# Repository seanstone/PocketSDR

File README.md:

# **Pocket SDR - An Open-Source GNSS SDR, ver. 0.12**

## **Modifications**

* Add .gitignore
* Submodules for LDPC-codes and libfec
* Ignore untracked in libfec submodule
* Executable python scripts
* Use pkg-config for compiler args
* Top-level makefile
* macOS support

--------------------------------------------------------------------------------

## **Overview**

Pocket SDR is an open-source GNSS (Global Navigation Satellite System) receiver
based on the SDR (software defined radio) technology. It consists of RF frontend
devices named "Pocket SDR FE", some utilities for the devices, and GNSS-SDR
APs (application programs) written in Python, C, and C++. It supports almost all
signals for GPS, GLONASS, Galileo, QZSS, BeiDou, NavIC, and SBAS.

The Pocket SDR FE device consists of 2 or 4 RF frontend channels, which support
GNSS L1 band (1525 - 1610 MHz), or L2/L5/L6 band (1160 - 1290 MHz). The bandwidth
of each RF channel covers up to 36 MHz. The sampling rate of the ADC can be
configured up to 32 Msps (FE 2CH) or 48 Msps (FE 4CH).

The Pocket SDR also contains some utility programs for the Pocket SDR FE devices,
to setup the devices, capture and dump the digitized IF (inter-frequency) data.
These utilities support Windows, Linux, Raspberry Pi OS, and other environments.
The Pocket SDR also provides GNSS-SDR APs to show the PSD (power spectrum
density) of captured IF data, search GNSS signals, track these signals, decode
navigation data and generate PVT (position, velocity and time) solutions. The
supported GNSS signals are as follows. For details on these signals and signal
IDs used in the APs, refer [Pocket SDR Signal IDs](/doc/signal_IDs.pdf).

* **GPS**: L1C/A, L1C-D, L1C-P, L2C-M, L5-I, L5-Q
* **GLONASS**: L1C/A (L1OF), L2C/A (L2OF), L1OCd, L1OCp, L2OCp, L3OCd, L3OCp
* **Galileo**: E1-B, E1-C, E5a-I, E5a-Q, E5b-I, E5b-Q, E6-B, E6-C
* **QZSS**: L1C/A, L1C/B, L1C-D, L1C-P, L1S, L2C-M, L5-I, L5-Q, L5S-I, L5S-Q, L6D, L6E
* **BeiDou**: B1I, B1C-D, B1C-P, B2a-D, B2a-P, B2I, B2b-I, B3I
* **NavIC**: L1-SPS-D, L1-SPS-P, L5-SPS
* **SBAS**: L1C/A, L5-I, L5-Q

These utilities and APs are written in Python, C, and C++ by very compact way. They
are easily modified by users to add user's unique algorithms. 

**<p style="text-align: center;">Pocket SDR FEs (FE 2CH v.2.1, FE 2CH v.2.3, and FE 4CH v.3.0)</p>**

The introduction of Pocket SDR is shown in the following slides.

T.Takasu, An Open Source GNSS SDR: Development and Application, IPNTJ Next GNSS
Technology WG, Feb 21, 2022
(https://gpspp.sakura.ne.jp/paper2005/IPNTJ_NEXTWG_202202.pdf)

For an application of Pocket SDR, refer the following slides.

T.Takasu, Development of QZSS L6 Receiver without Pilot Signal by using SDR,
IPNTJ Annual Conference, June 10, 2022
(https://gpspp.sakura.ne.jp/paper2005/IPNTJ_20220610.pdf)

--------------------------------------------------------------------------------

## **Directory Structure and Contents**
```
PocketSDR --+-- bin     Pocket SDR APs binary programs
            +-- app     Pocket SDR APs source programs
            |   +-- pocket_conf  Pocket SDR FE device configurator
            |   +-- pocket_dump  Dump digital IF data of Pocket SDR FE device
            |   +-- pocket_scan  Scan and list USB devices
            |   +-- pocket_acq   GNSS signal acquisition
            |   +-- pocket_trk   GNSS signal tracking and PVT generation
            |   +-- pocket_snap  Snapshot Positioning
            +-- src     Pocket SDR library source programs
            +-- python  Pocket SDR Python scripts
            +-- lib     Libraries for APs and Python scripts
            |   +-- win32        Libraries for Windows
            |   +-- linux        Libraries for Linux or Raspberry Pi OS
            |   +-- build        Makefiles to build libraries
            |   +-- cyusb        Cypress EZ-USB API (CyAPI.a) and includes
            |   +-- RTKLIB       RTKLIB source programs based on 2.4.3 b34
            |   +-- (libfec)     Library for FEC (forward error corrections) ([1])
            |   +-- (LDPC-codes) Library for LDPC-decoder ([2])
            +-- conf    Configuration files for Pocket SDR FE
            +-- FE_2CH  Pocket SDR FE 2CH H/W and F/W
            +-- FE_4CH  Pocket SDR FE 4CH H/W and F/W
            +-- driver  Windows driver for Pocket SDR FE
            +-- doc     Documents
            +-- image   Image files for documents
            +-- sample  Sample digital IF data captured by Pocket SDR FE
            +-- test    Test codes and data

            () : not included in the package
```

--------------------------------------------------------------------------------

## **Installation for Windows**

* Extract PocketSDR.zip or clone the git repository (https://github.com/tomojitakasu/PocketSDR)
 to an appropriate directory <install_dir>.
* Attach Pocket SDR FE to PC via USB cable.
* Install USB driver (CYUSB) for Pocket SDR RF frontend according to
  PocketSDR\driver\readme.txt.
* Add the Pocket SDR binary programs path (<install_dir>\PocketSDR\bin) to 
  the command search path (Path) of Windows environment variables.
* Add the Pocket SDR Python scripts path (<install_dir>\PocketSDR\python) to 
  the command search path (Path) of Windows environment variables.
* To rebuild the binary programs, you need MinGW64. Refer MSYS2 (https://www.msys2.org/)
for details.
* In MinGW64 environment, you need fftw3 library. To install fftw3 library.
```
$ pacman -S mingw-w64-x86_64-fftw
```

--------------------------------------------------------------------------------

## **Installation for Linux or Raspberry Pi OS**

* You need fundamental development packages and some libraries. Confirm the following
packages exist: gcc, g++, make, libusb-1.0-0-dev, libfftw3-dev, python3, python3-numpy,
python3-scipy, python3-matplotlib
* Extract PocketSDR.zip or clone the git repository to an appropriate directory <install_dir>.
```
$ unzip PocketSDR.zip
or
$ git clone https://github.com/tomojitakasu/PocketSDR
```
* Move to the library directory, install external library source trees ([1], [2]) as follows:
```
$ cd <install_dir>/lib
$ ./clone_lib.sh
```
* Move to the library build directory and build libraries.
```
$ cd <install_dir>/lib/build
$ make
$ make install
```
* Move to the application program directory and build utilities and APs.
```
$ cd <install_dir>/app
$ make
$ make install
```
* Add the Pocket SDR binary programs path (<install_dir>/PocketSDR/bin) to 
  the command search path.
* Usually you need to have a root permission to access USB devices. So you have to add
"sudo" to execute pocket_conf, pocket_dump like:
```
$ sudo pocket_conf ../conf/pocket_L1L6_12MHz.conf
$ sudo pocket_dump -t 10 ch1.bin ch2.bin
```

--------------------------------------------------------------------------------

## **Utility Programs for Pocket SDR FE**

Pocket SDR contains the following utility programs for the Pocket SDR FE.

- **pocket_conf**: Pocket SDR FE device configurator
- **pocket_scan**: Scan and list USB Devices
- **pocket_dump**: Capture and dump digital IF data of Pocket SDR FE device

For details, refer comment lines in src/pocket_conf.c, src/pocket_scan.c, 
src/pocket_dump.c.

--------------------------------------------------------------------------------

## **GNSS-SDR APs (Application Programs)**

Pocket SDR contains the following application programs for GNSS-SDR.

- **pocket_psd.py** : Plot PSD and histograms of digital IF data
- **pocket_acq.py** : GNSS signal acquisition in digital IF data
- **pocket_trk.py** : GNSS signal tracking and navigation data decoding in digital IF data
- **pocket_snap.py**: Snapshot positioning with digital IF data
- **pocket_plot.py**: Plot GNSS signal tracking log by pocket_trk.py
- **pocket_acq**    : C-version of pocket_acq.py (w/o graph plots)
- **pocket_trk**    : C-version of pocket_trk.py (w/o graph plots)
- **pocket_snap**   : C-version of pocket_snap.py

For details, refer comment lines in python/pocket_psd.py, python/pocket_acq.py,
python/pocket_trk.py, python/pocket_snap.py and python/pocket_plot.py. You need
Python 3, Numpy, Scipy and matplotlib to execute Python scripts.

--------------------------------------------------------------------------------

## **Execution Examples of Utility Programs and GNSS-SDR APs**

```
$ sudo pocket_conf
...
$ sudo pocket_conf conf/pocket_L1L6_12MHz.conf
Pocket SDR device settings are changed.
 
$ sudo pocket_dump -t 5 ch1.bin ch2.bin
  TIME(s)    T   CH1(Bytes)   T   CH2(Bytes)   RATE(Ks/s)
      5.0    I     60047360  IQ    120094720      11985.5

$ pocket_psd.py ch1.bin -f 12 -h
$ pocket_acq.py ch1.bin -f 12 -fi 3 -sig L1CA -prn 1-32,193-199
SIG= L1CA, PRN=   1, COFF=  0.23492 ms, DOP= -1519 Hz, C/N0= 33.6 dB-Hz
SIG= L1CA, PRN=   2, COFF=  0.98558 ms, DOP=  2528 Hz, C/N0= 33.8 dB-Hz
SIG= L1CA, PRN=   3, COFF=  0.96792 ms, DOP=  3901 Hz, C/N0= 33.7 dB-Hz
SIG= L1CA, PRN=   4, COFF=  0.96192 ms, DOP= -1957 Hz, C/N0= 40.4 dB-Hz
...
$ pocket_acq.py ch1.bin -f 12 -fi 3 -sig L1CA -prn 4

$ pocket_acq.py ch1.bin -f 12 -fi 3 -sig L1CA -prn 8 -3d

$ pocket_acq.py ch2.bin -f 12 -sig L6D -prn 194 -p

$ pocket_trk.py ch1.bin -f 12 -fi 3 -sig L1CA -prn 1-32
 TIME(s):      4.90                                                            SRCH:   0  LOCK:  9/ 32
 CH  SAT   SIG PRN  LOCK(s) C/N0 (dB-Hz)         COFF(ms) DOP(Hz)    ADR(cyc) SYNC  #NAV #ERR #LOL NER
  5  G05  L1CA   5     4.89 47.3 |||||||||||    0.7176882   958.2      4687.7 -B--     0    0    0   0
  6  G06  L1CA   6     4.89 41.7 |||||||        0.6283584 -3510.3    -17163.6 -B--     0    0    0   0
  7  G07  L1CA   7     4.89 40.5 |||||||        0.6468045 -1258.6     -6152.3 -B--     0    0    0   0
 11  G11  L1CA  11     4.89 46.7 |||||||||||    0.1002834 -1660.3     -8114.1 -B--     0    0    0   0
 13  G13  L1CA  13     4.89 47.8 |||||||||||    0.1235314  1803.9      8825.4 -B--     0    0    0   0
 15  G15  L1CA  15     4.89 40.3 ||||||         0.8688543  2864.4     14011.2 -B--     0    0    0   0
 20  G20  L1CA  20     4.89 46.5 ||||||||||     0.4835166  -161.2      -789.3 -B--     0    0    0   0
 29  G29  L1CA  29     4.89 44.5 |||||||||      0.4977522   429.7      2108.4 -B--     0    0    0   0
 30  G30  L1CA  30     4.89 44.2 |||||||||      0.7357694   540.2      2643.5 -B--     0    0    0   0
...
$ pocket_trk.py ch1.bin -f 12 -fi 3 -sig E1B -prn 18 -p
...
$ pocket_trk.py ch2.bin -f 12 -sig E6B -prn 4 -log trk.log -p -ts 0.2
...
``` 

--------------------------------------------------------------------------------

## **Real-time GNSS Signal Tracking with Pocket SDR FE and pocket_trk AP**

With the Pocket SDR FE device and the AP pocket_trk, you can track GNSS signals
and generate PVT solutions in real-time. In this case, the sampling frequency,
IF frequencies, sampling type (I or I/Q), RF channel selections are automatically
configured according to the device info obtained from the device. Multiple GNSS
signals and PRN numbers can be specified as pocket_trk options -sig and -prn.
On Linux or Raspberry Pi OS, you might have to add "sudo" to access the Pocket SDR FE
device.

``` 
$ pocket_trk -sig L1CA -prn 1-32 -sig L5I -prn 1-32
``` 

As default, the signal tracking status are shown as the following example.

``` 
 2024-05-30 08:39:50.996  35.1234065  138.1234560  1234.45  8/ 9 FIX      BUFF:  1% SRCH: 17 LOCK: 11/ 32
 CH RF  SAT   SIG PRN  LOCK(s) C/N0 (dB-Hz)         COFF(ms) DOP(Hz)    ADR(cyc) SYNC  #NAV #ERR #LOL FEC
  5  1  G05  L1CA   5    52.14 47.5 |||||||||||    0.6361186   779.8     41233.8 -BFR     7    0    0   0
  6  1  G06  L1CA   6    52.05 40.7 |||||||        0.0092524 -3740.1   -194068.1 -BF-     7    0    0   0
 ...
``` 

The first line of the status indicates:

```
2024-05-30 08:39:50.996: Signal reception time expressed in GPS time
 35.1234065 : PVT solution latitude  (deg, +: north, -: south)
138.1234560 : PVT solution longitude (deg, +: east, -: west)
1234.45     : PVT solution ellipsoidal height (m)
8/ 9        : Numbers of satellites for PVT and all tracking satellites
FIX         : FIX PVT fixed, --- PVT not available
BUFF:  1%   : Internal IF data buffer usage rate (overloaded if exceeding 100%)
SRCH: 17    : Signal search channel number
LOCK: 11/ 32: Numbers of signal lock channels and all channels
```

The third and following lines of the status indicates:

```
CH  : Receiver channel number (1-999)
RF  : RF frontend RF channel number (1-4)
SAT : GNSS satellite (Gnn: GPS, Rnn: GLONASS, Enn: Galileo, Jnn: QZSS,
      Cnn: BeiDou, Inn: NavIC, Snn: SBAS)
SIG : GNSS signal ID
PRN : PRN number or FCN for GLONASS FDMA
LOCK: Continuos lock time (s)
C/N0: C/N0 (dB-Hz) and C/N0 bar
COFF: Tracking PRN code offset (ms)
DOP : Doppler frequency (Hz)
ADR : Accumulated Doppler range (cycle)
SYNC: Synchronization status (secondary code, bit, frame, and polarity)
#NAV: Number of properly decoded navigation subframes or messages
#ERR: Number of error navigation subframes or messages
#LOL: Number of loss-of-lock trackings
FEC : Number of corrected error bits by FEC (-1: unrecoverable errors)
```

The GNSS PVT solutions can be output as NMEA 0183 format ([3]) by -nmea option.

``` 
$ pocket_trk -sig L1CA -prn 1-32 -nmea <path>
``` 

The path is just a local file path. To output data to outside of the AP,
use :port as the path to accept connections by a TCP server, or address:port
to connect an external TCP server.

The GNSS observation data and navigation data can be output as RTCM3 MSM7 and
navigation data formats ([4]) by -rtcm option.

``` 
$ pocket_trk -sig L1CA -prn 1-32 -rtcm <path>
``` 

The GNSS signal tracking log including observation data and HEX dump of navigation
data can be output by -log option.

``` 
$ pocket_trk -sig L1CA -prn 1-32 -log <path>
``` 

--------------------------------------------------------------------------------

## **References**

[1] https://github.com/quiet/libfec

[2] https://github.com/radfordneal/LDPC-codes

[3] NMEA 0183, Standard for Interfacing Marine Electronic Devices, National Marine
Electronics Association and International Marine Electronics Assosiation, 2013

[4] RTCM 10403.3 with Amendment 1, Differential GNSS (Global Navgation Satellite
Systems) service - version 3, Radio Technical Commission for Maritime Services,
April 28, 2020

--------------------------------------------------------------------------------

## **History**

* 2021-10-20  0.1  1st draft version
* 2021-10-25  0.2  Add Rebuild F/W and Write F/W Image to PocketSDR
* 2021-12-01  0.3  Add and modify Python scripts
* 2021-12-25  0.4  Add and modify Python scripts
* 2022-01-05  0.5  Fix several problems.
* 2022-01-13  0.6  Add and modify Python scripts
* 2022-02-15  0.7  Improve performance, Add some Python scripts.
* 2022-07-08  0.8  Add C-version of pocket_acq.py and pocket_trk.py.
* 2024-01-03  0.9  Add C-version of pocket_snap.py.
                   pocket_trk supports multi-signal and multi-threading
* 2024-01-12  0.10 Support NavIC L1-SPS-D, L1-SPS-P, GLONASS L1OCd, L1OCp and L2OCp.
* 2024-01-25  0.11 Support decoding of GLONASS L1OCd NAV data
                   Support NB-LDCP error correction for BDS B1C, B2a and B2b
* 2024-05-28  0.12 Performance optimized.
                   Support PVT generation, RTCM3 and NMEA outputs

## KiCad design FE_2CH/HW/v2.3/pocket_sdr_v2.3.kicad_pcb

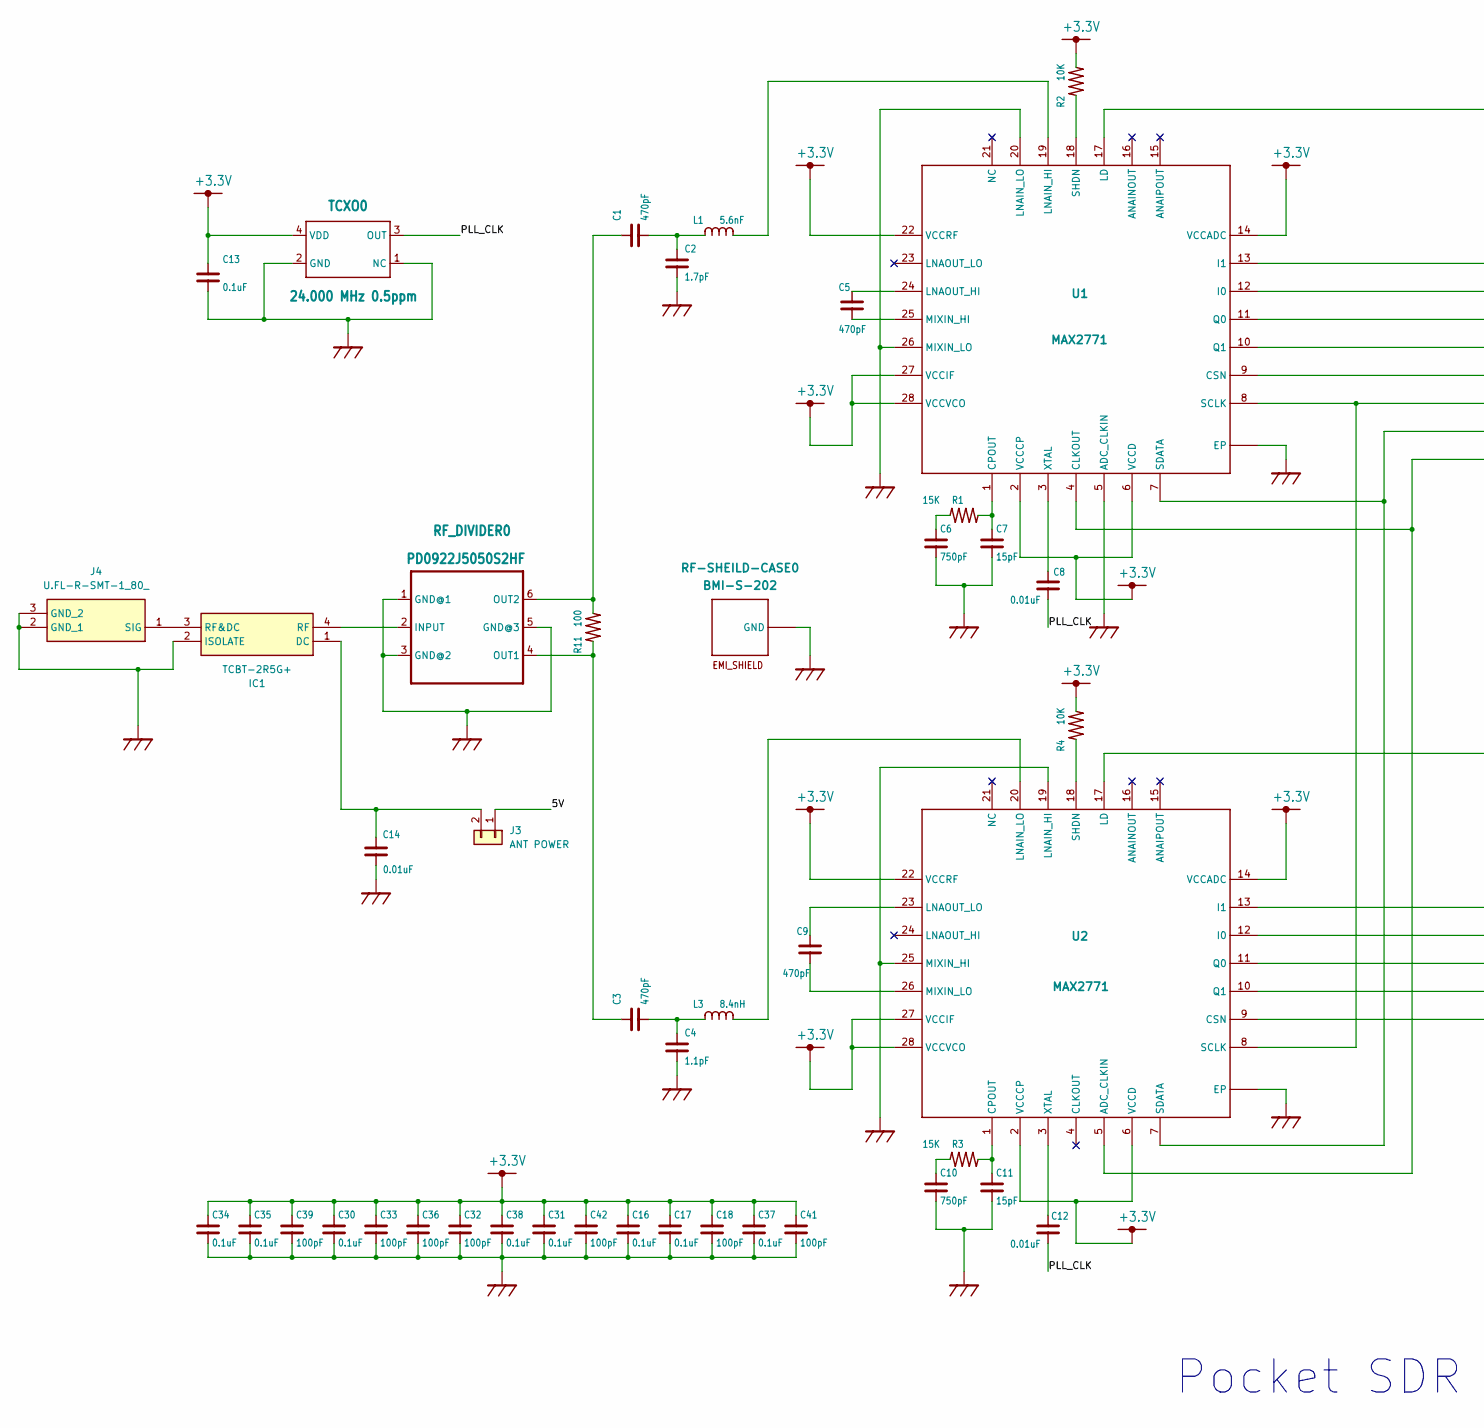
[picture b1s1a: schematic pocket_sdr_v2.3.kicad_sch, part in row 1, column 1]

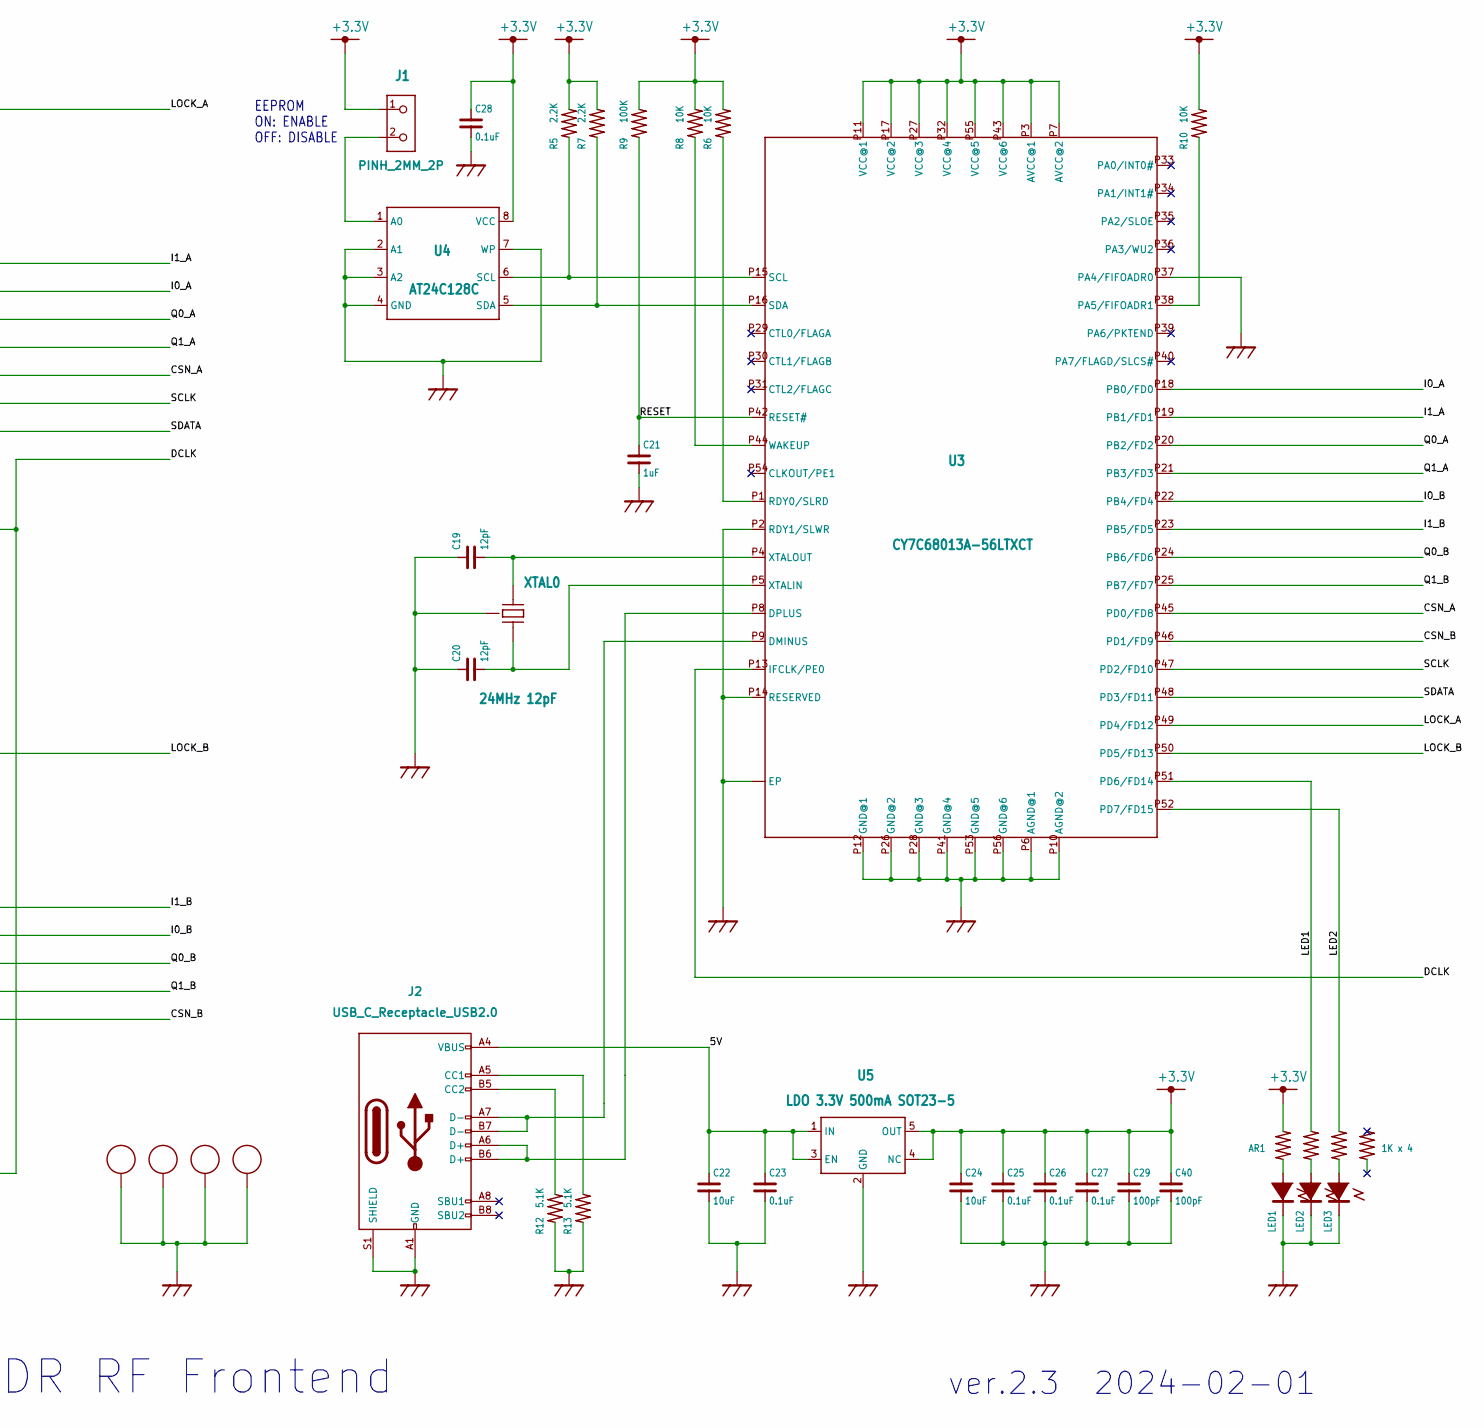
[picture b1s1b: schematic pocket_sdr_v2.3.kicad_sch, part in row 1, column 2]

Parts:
AR1: 1K x 4; EXB28V; LCSC C192510
C1, C3, C5, C9: 470pF; C1005; LCSC C106207
C2: 1.7pF; C1005; LCSC C161313
C4: 1.1pF; C1005; LCSC C541332
C6, C10: 750pF; C1005; LCSC C710656
C7, C11: 15pF; C1005; LCSC C1548
C8, C12: 0.01uF; C1005; LCSC C327009
C13, C16, C17, C23, C25, C26, C27, C28, C30, C31, C34, C35, C37, C38: 0.1uF; C1005; LCSC C1525
C14: 0.01uF; C1005; LCSC C1546
C18, C29, C32, C33, C36, C39, C40, C41, C42: 100pF; C1005; LCSC C1546
C19, C20: 12pF; C1005; LCSC C1547
C21: 1uF; C1005; LCSC C14445
C22, C24: 10uF; C3225; LCSC C730480
IC1: TCBT-2R5G+; TCBT2R5G; Mouser Part Number 139-TCBT-2R5G
J1: PINH_2MM_2P; PINH-2MM-2P
J2: USB_C_Receptacle_USB2.0; USB_C_Receptacle_GCT_USB4105-xx-A_16P_TopMnt_Horizontal; LCSC C3025063
J3: ANT POWER; PinHeader_1x02_P2.00mm_Vertical
J4: U.FL-R-SMT-1_80_; UFLRSMT180; Mouser Part Number 798-UFLRSMT180
L1: 5.6nF; C1608; LCSC C98081
L3: 8.4nH; C1608; LCSC C346331
LED1, LED2, LED3: LED1608; LED_1608; LCSC C2290
R1, R3: 15K; C1005; LCSC C137917
R2, R4, R6, R8, R10: 10K; C1005; LCSC C60489
R5, R7: 2.2K; C1005; LCSC C163447
R9: 100K; C1005; LCSC C106234
R11: 100; C1005; LCSC C106233
R12, R13: 5.1K; C1005; LCSC C25905
RF-SHEILD-CASE0: BMI-S-202
RF_DIVIDER0: PD0922J5050S2HF; RF_DIV; LCSC C5136968
TCXO0: 24.000 MHz 0.5ppm; TCXO; LCSC C7528445
U1, U2: MAX2771; TQFN28; LCSC C400143
U3: CY7C68013A-56LTXCT; QFN56; LCSC C14912
U4: AT24C128C; TSSOP_8P; LCSC C616767
U5: LDO 3.3V 500mA SOT23-5; SOT23; LCSC C3749679
XTAL0: 24MHz 12pF; XTAL_SMD; LCSC C255917

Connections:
+3.3V: AR1.2, C13.1, C16.1, C17.1, C18.1, C24.P$1 (1), C25.1, C26.1, C27.1, C28.1, C29.1, C30.1, C31.1, C32.1, C33.1, C34.1, C35.1, C36.1, C37.1, C38.1, C39.1, C40.1, C41.1, C42.1, J1.1, R2.2, R4.2, R5.2, R6.2, R7.2, R8.2, R9.2, R10.2, TCXO0.4 (VDD), U1.2 (VCCCP), U1.6 (VCCD), U1.14 (VCCADC), U1.22 (VCCRF), U1.27 (VCCIF), U1.28 (VCCVCO), U2.2 (VCCCP), U2.6 (VCCD), U2.14 (VCCADC), U2.22 (VCCRF), U2.27 (VCCIF), U2.28 (VCCVCO), U3.P3 (AVCC@1), U3.P7 (AVCC@2), U3.P11 (VCC@1), U3.P17 (VCC@2), U3.P27 (VCC@3), U3.P32 (VCC@4), U3.P43 (VCC@6), U3.P55 (VCC@5), U4.8 (VCC), U5.4 (NC), U5.5 (OUT)
/5V: C22.P$1 (1), C23.1, J2.A4 (VBUS), J2.A9 (VBUS), J2.B4 (VBUS), J2.B9 (VBUS), J3.1, U5.1 (IN), U5.3 (EN)
/CSN_A: U1.9 (CSN), U3.P45 (PD0/FD8)
/CSN_B: U2.9 (CSN), U3.P46 (PD1/FD9)
/DCLK: U1.4 (CLKOUT), U2.5 (ADC_CLKIN), U3.P13 (IFCLK/PE0)
/I0_A: U1.12 (I0), U3.P18 (PB0/FD0)
/I0_B: U2.12 (I0), U3.P22 (PB4/FD4)
/I1_A: U1.13 (I1), U3.P19 (PB1/FD1)
/I1_B: U2.13 (I1), U3.P23 (PB5/FD5)
/LED1: AR1.4, U3.P51 (PD6/FD14)
/LED2: AR1.6, U3.P52 (PD7/FD15)
/LOCK_A: U1.17 (LD), U3.P49 (PD4/FD12)
/LOCK_B: U2.17 (LD), U3.P50 (PD5/FD13)
/PLL_CLK: C8.1, C12.1, TCXO0.3 (OUT)
/Q0_A: U1.11 (Q0), U3.P20 (PB2/FD2)
/Q0_B: U2.11 (Q0), U3.P24 (PB6/FD6)
/Q1_A: U1.10 (Q1), U3.P21 (PB3/FD3)
/Q1_B: U2.10 (Q1), U3.P25 (PB7/FD7)
/RESET: C21.1, R9.1, U3.P42 (RESET#)
/SCLK: U1.8 (SCLK), U2.8 (SCLK), U3.P47 (PD2/FD10)
/SDATA: U1.7 (SDATA), U2.7 (SDATA), U3.P48 (PD3/FD11)
CPAD_2.2MM: C2.1, C4.2, C6.2, C7.2, C10.2, C11.2, C13.2, C14.1, C16.2, C17.2, C18.2, C19.1, C20.1, C21.2, C22.P$2 (2), C23.2, C24.P$2 (2), C25.2, C26.2, C27.2, C28.2, C29.2, C30.2, C31.2, C32.2, C33.2, C34.2, C35.2, C36.2, C37.2, C38.2, C39.2, C40.2, C41.2, C42.2, IC1.2 (ISOLATE), J2.A1 (GND), J2.A12 (GND), J2.B1 (GND), J2.B12 (GND), J2.S1 (SHIELD), J4.2 (GND_1), J4.3 (GND_2), LED1.2, LED2.2, LED3.2, R12.1, R13.1, RF-SHEILD-CASE0.P1 (GND), RF-SHEILD-CASE0.P2 (GND), RF-SHEILD-CASE0.P3 (GND), RF-SHEILD-CASE0.P4 (GND), RF-SHEILD-CASE0.P5 (GND), RF-SHEILD-CASE0.P6 (GND), RF-SHEILD-CASE0.P7 (GND), RF-SHEILD-CASE0.P8 (GND), RF-SHEILD-CASE0.P9 (GND), RF-SHEILD-CASE0.P10 (GND), RF-SHEILD-CASE0.P11 (GND), RF-SHEILD-CASE0.P12 (GND), RF_DIVIDER0.1 (GND@1), RF_DIVIDER0.3 (GND@2), RF_DIVIDER0.5 (GND@3), TCXO0.1 (NC), TCXO0.2 (GND), U1.5 (ADC_CLKIN), U1.20 (LNAIN_LO), U1.26 (MIXIN_LO), U1.C1 (EP), U1.C2 (EP), U1.C3 (EP), U1.C4 (EP), U1.EP, U1.V1 (EP), U1.V2 (EP), U1.V3 (EP), U1.V4 (EP), U1.V5 (EP), U1.V6 (EP), U1.V7 (EP), U1.V8 (EP), U1.V9 (EP), U2.19 (LNAIN_HI), U2.25 (MIXIN_HI), U2.C1 (EP), U2.C2 (EP), U2.C3 (EP), U2.C4 (EP), U2.EP, U2.V1 (EP), U2.V2 (EP), U2.V3 (EP), U2.V4 (EP), U2.V5 (EP), U2.V6 (EP), U2.V7 (EP), U2.V8 (EP), U2.V9 (EP), U3.EP1 (EP), U3.EP2 (EP), U3.EP3 (EP), U3.EP4 (EP), U3.EP5 (EP), U3.P2 (RDY1/SLWR), U3.P6 (AGND@1), U3.P10 (AGND@2), U3.P12 (GND@1), U3.P14 (RESERVED), U3.P26 (GND@2), U3.P28 (GND@3), U3.P37 (PA4/FIFOADR0), U3.P41 (GND@4), U3.P53 (GND@5), U3.P56 (GND@6), U3.P$1 (EP), U3.P$2 (EP), U3.P$3 (EP), U3.P$4 (EP), U3.P$5 (EP), U3.P$6 (EP), U3.P$7 (EP), U3.P$8 (EP), U3.P$9 (EP), U3.P$10 (EP), U3.P$11 (EP), U3.P$12 (EP), U3.P$13 (EP), U3.P$14 (EP), U3.P$15 (EP), U3.P$16 (EP), U3.P$17 (EP), U3.P$18 (EP), U3.P$19 (EP), U3.P$20 (EP), U4.2 (A1), U4.3 (A2), U4.4 (GND), U4.7 (WP), U5.2 (GND), XTAL0.P2 (GND), XTAL0.P4 (GND)
unnamed: AR1.1, LED1.1 (+)
unnamed: AR1.3, LED2.1 (+)
unnamed: AR1.5, LED3.1 (+)
unnamed: C14.2, IC1.1 (DC), J3.2
unnamed: IC1.3 (RF&DC), J4.1 (SIG)
unnamed: IC1.4 (RF), RF_DIVIDER0.2 (INPUT)
unnamed: J1.2, U4.1 (A0)
unnamed: J2.A5 (CC1), R13.2
unnamed: J2.B5 (CC2), R12.2
unnamed: C1.2, C2.2, L1.1
unnamed: L1.2, U1.19 (LNAIN_HI)
unnamed: C3.2, C4.1, L3.1
unnamed: L3.2, U2.20 (LNAIN_LO)
unnamed: C6.1, R1.1
unnamed: C7.1, R1.2, U1.1 (CPOUT)
unnamed: R2.1, U1.18 (SHDN)
unnamed: C10.1, R3.1
unnamed: C11.1, R3.2, U2.1 (CPOUT)
unnamed: R4.1, U2.18 (SHDN)
unnamed: R5.1, U3.P15 (SCL), U4.6 (SCL)
unnamed: R6.1, U3.P1 (RDY0/SLRD)
unnamed: R7.1, U3.P16 (SDA), U4.5 (SDA)
unnamed: R8.1, U3.P44 (WAKEUP)
unnamed: R10.1, U3.P38 (PA5/FIFOADR1)
unnamed: C3.1, R11.1, RF_DIVIDER0.4 (OUT1)
unnamed: C1.1, R11.2, RF_DIVIDER0.6 (OUT2)
unnamed: C5.1, U1.24 (LNAOUT_HI)
unnamed: C5.2, U1.25 (MIXIN_HI)
unnamed: C8.2, U1.3 (XTAL)
unnamed: C9.1, U2.23 (LNAOUT_LO)
unnamed: C9.2, U2.26 (MIXIN_LO)
unnamed: C12.2, U2.3 (XTAL)
unnamed: J2.A7 (D-), J2.B7 (D-), U3.P9 (DMINUS)
unnamed: J2.A6 (D+), J2.B6 (D+), U3.P8 (DPLUS)
unnamed: C20.2, U3.P5 (XTALIN), XTAL0.P3 (XTAL2)
unnamed: C19.2, U3.P4 (XTALOUT), XTAL0.P1 (XTAL1)

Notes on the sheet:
Pocket SDR RF Frontend
EEPROM ON: ENABLE OFF: DISABLE
ver.2.3 2024-02-01

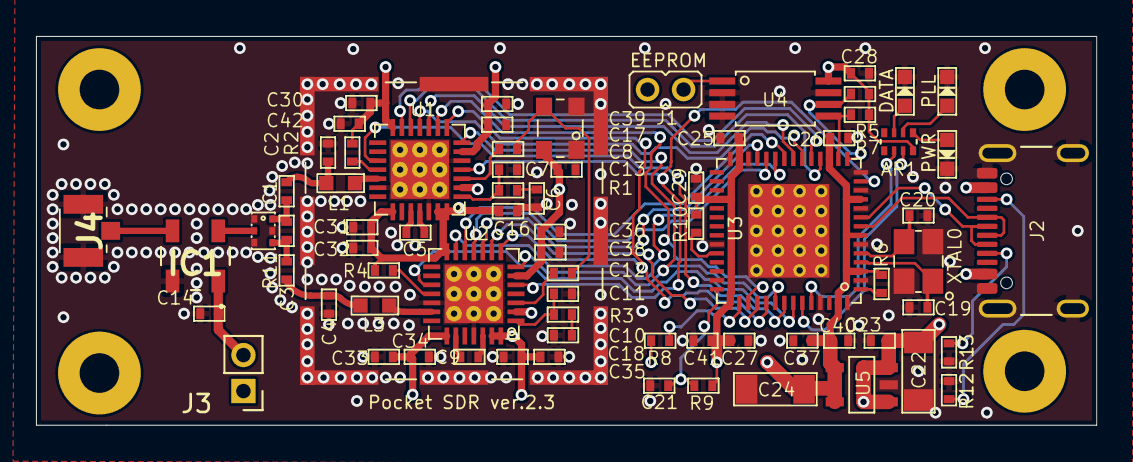
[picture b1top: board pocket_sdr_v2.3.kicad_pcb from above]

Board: 4 copper layers, 58.9 x 21.6 mm, 74 parts (0 on the bottom side), 58 nets.

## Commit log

2023-09-02 git ignore build files
2023-09-02 Add LDPC-codes submodule
2023-09-02 Add libfec submodule
2023-09-02 Add RTKLIB submodule
2023-09-02 Ignore changes to submodules
2023-09-02 Fix build options for pocket_scan
2023-09-02 git ignore built apps
2023-09-02 Make python apps executable
2023-09-02 git ignore .bin files
2023-09-02 git ignore __pycache__
2023-09-02 RTKLIB compat for macOS
2023-09-02 libfec compat for macOS
2023-09-02 Use own fork for RTKLIB submodule
2023-09-14 update submodule link
2023-09-15 update some operation instructions
2023-09-15 Update readme instructions
2023-09-18 fix: build libsdr on macOS
2023-09-18 fix: build flags and include dirs on macOS
2023-09-18 fix: python load rtklib on mac
2023-09-20 feat: log libusb transfer overflow error
2023-09-20 fix: libusb buffer allocation on mac
2023-09-20 fix: dynamic lib loading on mac
2023-09-20 feat: add top level makefile
2023-09-20 feat: remove user files
2023-09-21 fix: top level makefile
2023-09-24 Print to stderr for apps
2023-09-24 Modify FFTW wisdom path
2023-09-24 Generate fftw wisdom with makefile
2024-01-05 fix: fftw_wisdom.txt dependency
2024-01-12 git gnore pocket_snap
2024-01-12 Modify fft_wisdom.txt default path
2024-01-14 libsdr support for macOS
2024-01-14 Fix conversion to uint8_t
2024-01-15 git ignore fftw_wisdom
2024-01-16 feat: git don't track fftw_wisdom.txt
2024-06-10 Add .gitignore
2024-06-10 Submodules for LDPC-codes and libfec
2024-06-10 Executable python scripts
2024-06-10 Ignore untracked in libfec submodule
2024-06-10 Use pkg-config for compiler args
2024-06-10 Top-level makefile
2024-06-10 macOS support
2024-06-10 Move modifications to top of README
2024-06-14 git ignore fp-info-cache and .DS_Store
2024-06-16 JLCPCB mappings
2024-06-16 Export BOM
2024-06-16 Alternative JLCPCB mappings
2024-06-16 Update JLCPCB mappings
2024-06-16 Fix USB-C footprint assignment
2024-06-16 Put back bias tee and U.FL connector
2024-06-17 git ignore .pocket_navdata.csv
2024-06-17 Add kissfft lib
2024-06-17 Use kissfft
2024-06-22 Support cross compile for libfec
2024-06-22 Support cross compile for libsdr
2024-06-22 Support cross compile for app
2024-06-22 Support cross compile for pocket_trk
2024-06-22 Support for cross compile
